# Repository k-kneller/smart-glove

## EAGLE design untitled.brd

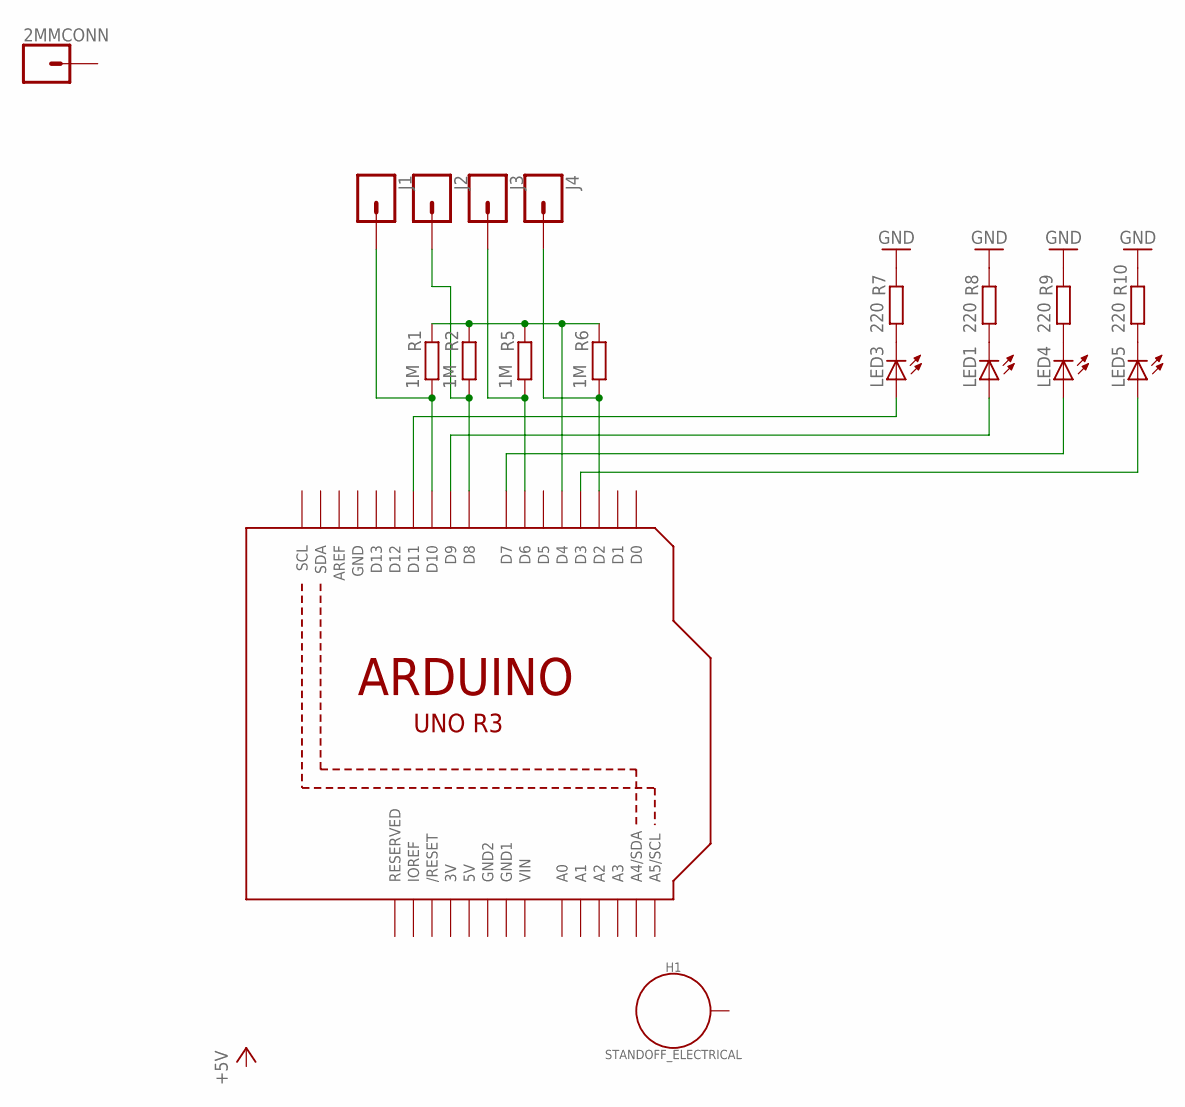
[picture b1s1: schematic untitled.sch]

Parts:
2MMCONN: CONN_01PTH_2MM; 1X01_2MM
H1: STANDOFF_ELECTRICAL; STANDOFF-ELECTRICAL
J1, J2, J3, J4: CONN_01; 1X01
LED1, LED3, LED4, LED5: LED3MM
R1, R2, R5, R6: 1M; 0207/10
R7, R8, R9, R10: 220; 0207/10
U1: ARDUINOR3-DIMENSION; ARDUINOR3

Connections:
3V: U1.3V
5V: U1.5V
GND: R7.2, R8.2, R9.2, R10.2, U1.GND
GND1: U1.GND1
GND2: U1.GND2
unnamed: J1.1, R1.1, U1.D10
unnamed: R1.2, R2.2, R5.2, R6.2, U1.D4
unnamed: LED5.A, U1.D3
unnamed: J4.1, R6.1, U1.D2
unnamed: J3.1, R5.1, U1.D6
unnamed: J2.1, R2.1, U1.D8
unnamed: LED4.A, U1.D7
unnamed: LED1.A, U1.D9
unnamed: LED3.K (C), R7.1
unnamed: LED3.A, U1.D11
unnamed: LED1.K (C), R8.1
unnamed: LED4.K (C), R9.1
unnamed: LED5.K (C), R10.1
VIN: U1.VIN

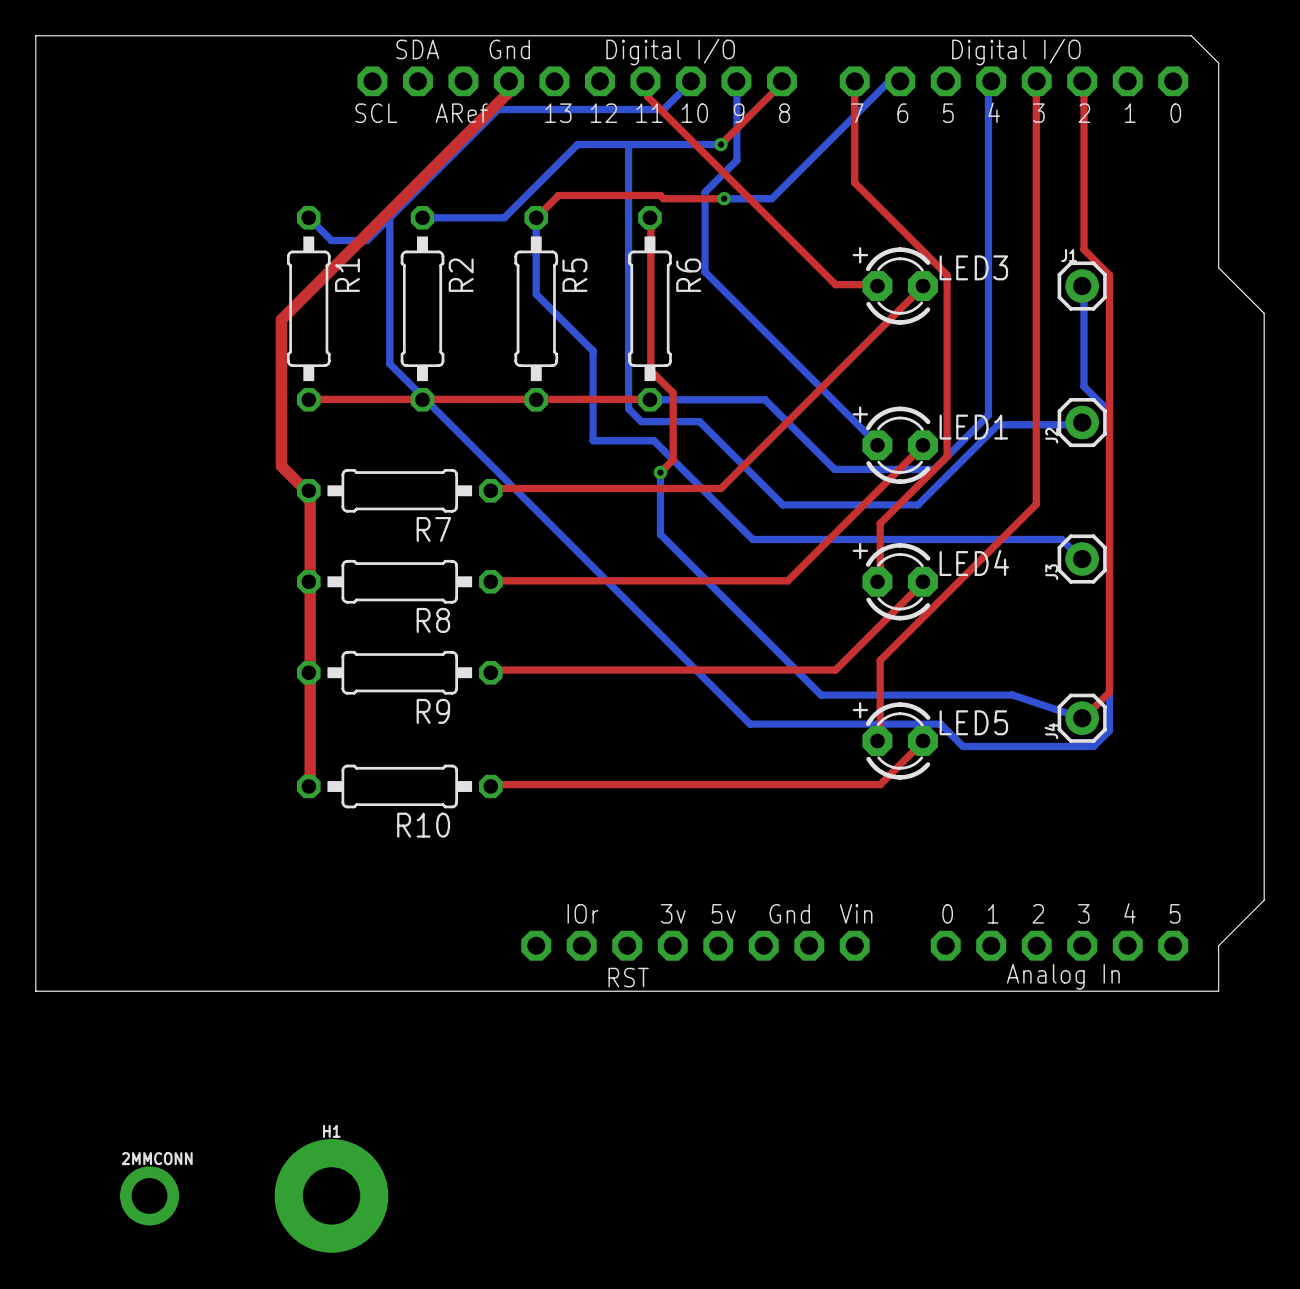
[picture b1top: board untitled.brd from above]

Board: 2 copper layers, 68.6 x 53.3 mm, 19 parts (0 on the bottom side), 14 nets.

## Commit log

2022-04-17 Create fusion schematics
2022-04-17 Create arduino code
2022-04-17 Create Python game code

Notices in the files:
parts and their libraries:
SparkFun-Connectors: Licensing: Creative Commons ShareAlike 4.0 International - https://creativecommons.org/licenses/by-sa/4.0
